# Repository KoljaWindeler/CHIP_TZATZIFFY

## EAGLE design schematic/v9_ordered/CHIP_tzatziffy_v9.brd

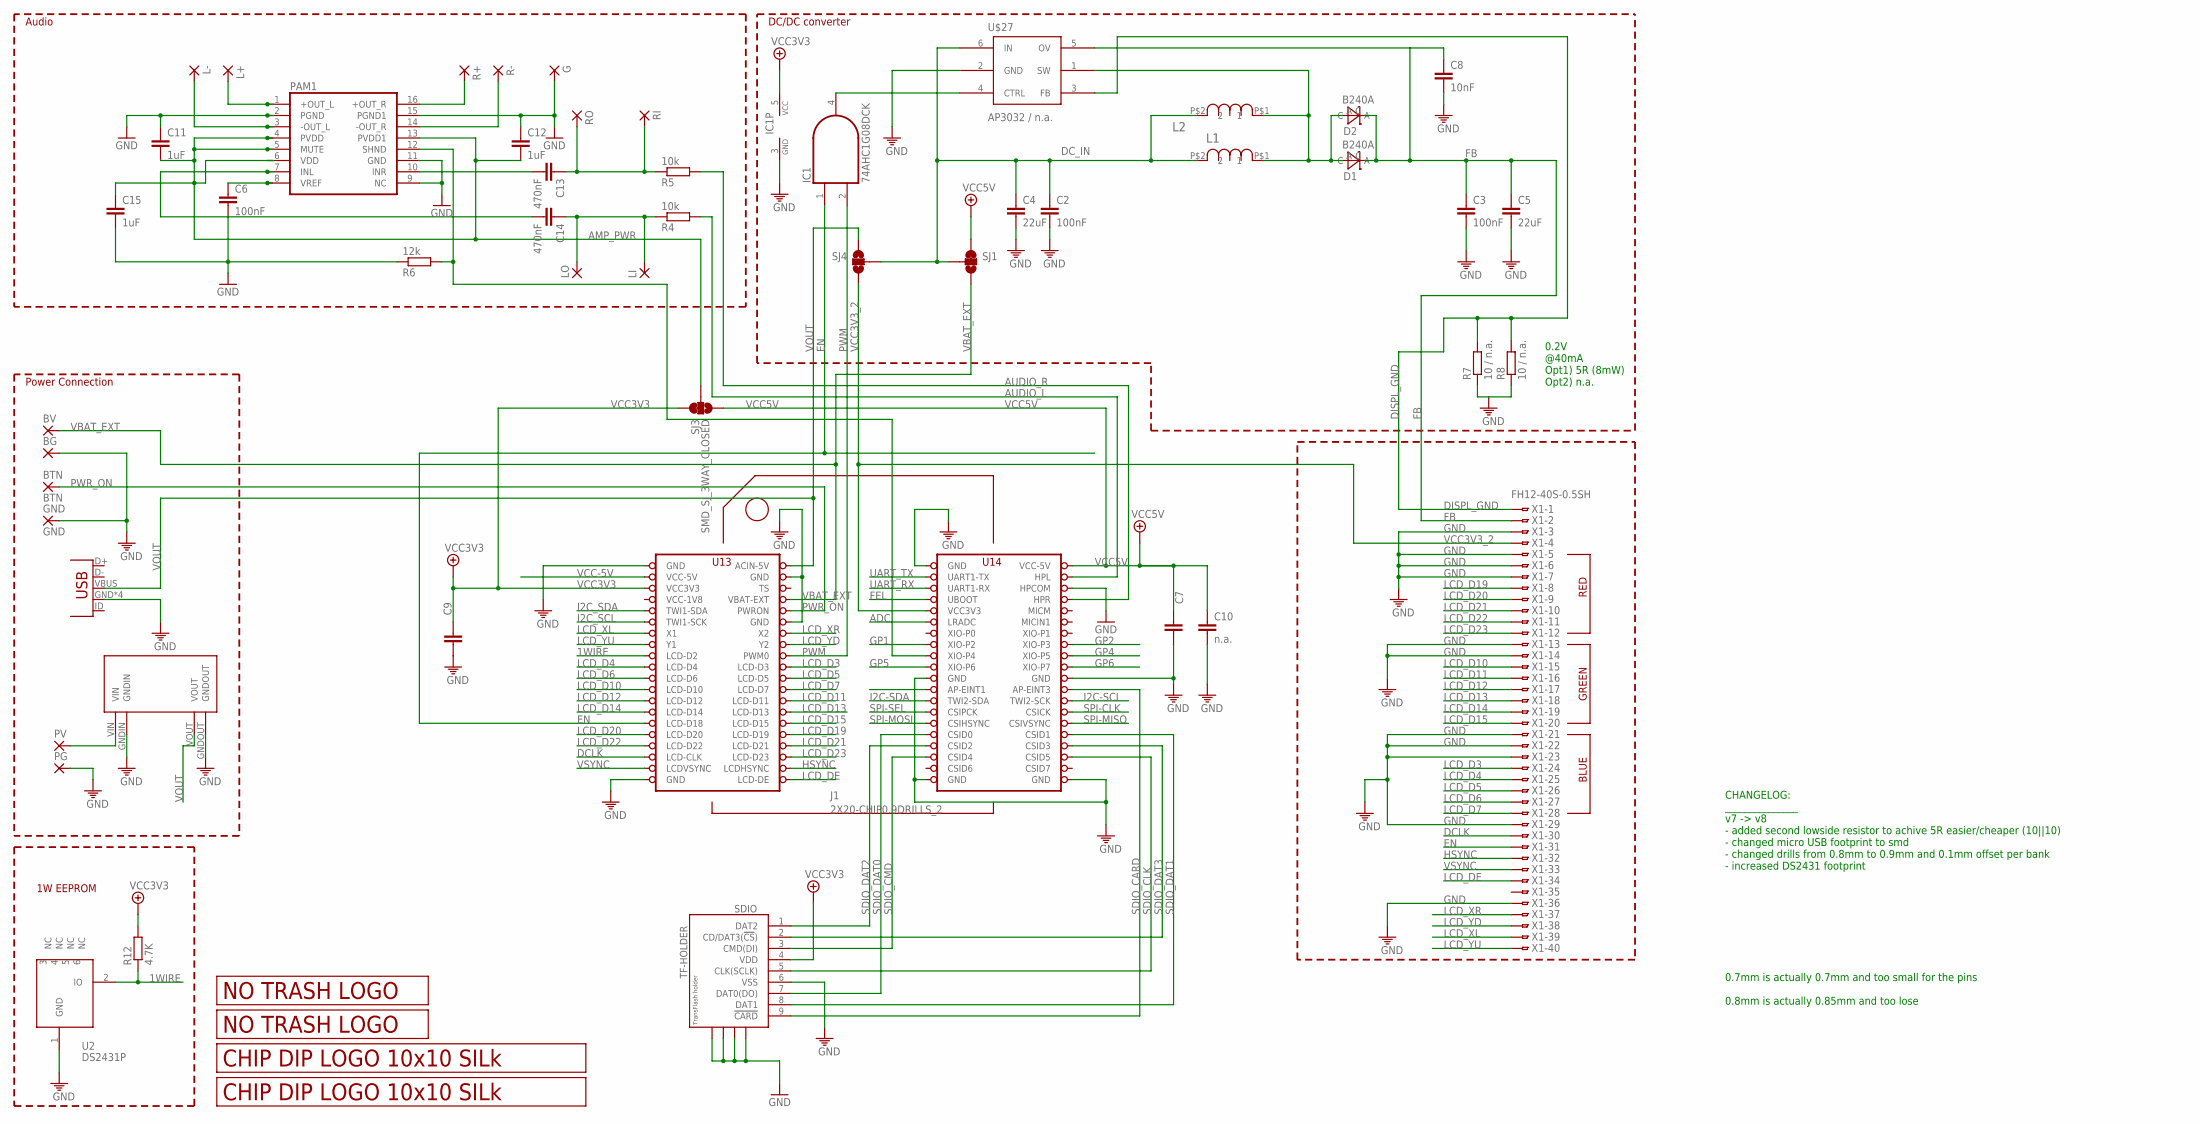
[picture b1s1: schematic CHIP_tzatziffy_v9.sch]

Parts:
BG: 1,6/0,8
BTN: BTN; SMD1,27-2,54
BV: 1,6/0,8
C2, C3, C6: 100nF; C0805
C4, C5: 22uF; C1206
C7, C9, C10: n.a.; C0805
C8: 10nF; C0805
C11, C12, C15: 1uF; C0805
C13, C14: 470nF; C0805
D1, D2: B240A; DO-214AC
G: 1,6/0,8
GND: GND; SMD1,27-2,54
IC1: 74AHC1G08DCK; SC70-5
J1: 2X20-CHIP0.9DRILLS_2; 2X20CHIP_BANK_OFFSET_TH_0.9
JP1: USBMICRO_SMD; USB-B-MICRO-SMD_V03
L1, L2: SRN6045-100M; SRN6045
L+: 1,6/0,8
L-: 1,6/0,8
LI: 1,6/0,8
LO: 1,6/0,8
PAM1: PAM8403; SOP-16
PG: 1,6/0,8
PV: 1,6/0,8
R4, R5: 10k; R0805
R6: 12k; R0805
R7, R8: 10 / n.a.; M0805
R12: 4.7K; M0805
R+: 1,6/0,8
R-: 1,6/0,8
RI: 1,6/0,8
RO: 1,6/0,8
SDIO: TF-HOLDER; TF-PULL
SJ1, SJ3: SMD_SJ_3WAY_CLOSED
SJ4: SMD_SJ_3WAY_OPENT; SMD_SJ_3WAY_OPEN
U2: DS2431P; TSOC6
U$2, U$5: LOGO_10X10_SILK; LOGO2_10X10_SILK
U$3: LOGO_NO_TRASHROHS; LOGO_ROHS_SYM
U$4: LOGO_NO_TRASHNO_TRASH; LOGO_ROHS_NO_TRASH
U$10: MP1584EN_FRAMELESS
U$27: AP3032 / n.a.; SOT23-6
X1: FH12-40S-0.5SH

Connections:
1WIRE: J1.LCD-D2, R12.1, U2.2 (IO)
ADC: J1.LRADC
AMP_PWR: C11.2, C12.2, C15.1, PAM1.4 (PVDD), PAM1.5 (MUTE), PAM1.6 (VDD), PAM1.13 (PVDD1), SJ3.2
AUDIO_L: J1.HPL, R4.2
AUDIO_R: J1.HPR, R5.2
DCLK: J1.LCD-CLK, X1.30
DC_IN: C2.1, C4.1, L1.P$2 (2), L2.P$2 (2), SJ1.2, SJ4.2, U$27.6 (IN)
DISPL_GND: R7.2, R8.2, U$27.3 (FB), X1.1
EN: IC1.1 (I0), J1.LCD-D18, X1.31
FB: C3.1, C5.1, C8.1, D1.C, D2.C, U$27.5 (OV), X1.2
FEL: J1.FEL (UBOOT)
GND: BG.1, C2.2, C3.2, C4.2, C5.2, C6.2, C7.2, C8.2, C9.2, C10.2, C11.1, C12.1, C15.2, G.1, GND.1, IC1.3 (GND), J1.GND@1 (GND), J1.GND@2 (GND), J1.GND@3 (GND), J1.GND@4 (GND), J1.GND@5 (GND), J1.GND@6 (GND), J1.GND@7 (GND), J1.GND@8 (GND), J1.GND@10 (GND), J1.HPCOM, JP1.GND, JP1.SHIELD1 (GND), JP1.SHIELD2 (GND), JP1.SHIELD3 (GND), PAM1.2 (PGND), PAM1.9 (NC), PAM1.11 (GND), PAM1.15 (PGND1), PG.1, R6.1, R7.1, R8.1, SDIO.6 (VSS), SDIO.S1, SDIO.S2, SDIO.S3, SDIO.S4, U2.1 (GND), U$10.GNDIN, U$10.GNDOUT, U$27.2 (GND), X1.3, X1.5, X1.6, X1.7, X1.13, X1.14, X1.21, X1.22, X1.23, X1.29, X1.36
GP1: J1.XIO-P2
GP2: J1.XIO-P3
GP3: J1.XIO-P4, PAM1.12 (SHND), R6.2
GP4: J1.XIO-P5
GP5: J1.XIO-P6
GP6: J1.XIO-P7
HSYNC: J1.LCD-HSYNC (LCDHSYNC), X1.32
I2C-SCL: J1.TWI2-SCK
I2C-SDA: J1.TWI2-SDA
I2C_SCL: J1.TWI1-SCK
I2C_SDA: J1.TWI1-SDA
INL: C14.2, PAM1.7 (INL)
INR: C13.2, PAM1.10 (INR)
KPD_INT: J1.AP-EINT1
L+OUT: L+.1, PAM1.1 (+OUT_L)
L-OUT: L-.1, PAM1.3 (-OUT_L)
LCD_D3: J1.LCD-D3, X1.24
LCD_D4: J1.LCD-D4, X1.25
LCD_D5: J1.LCD-D5, X1.26
LCD_D6: J1.LCD-D6, X1.27
LCD_D7: J1.LCD-D7, X1.28
LCD_D10: J1.LCD-D10, X1.15
LCD_D11: J1.LCD-D11, X1.16
LCD_D12: J1.LCD-D12, X1.17
LCD_D13: J1.LCD-D13, X1.18
LCD_D14: J1.LCD-D14, X1.19
LCD_D15: J1.LCD-D15, X1.20
LCD_D19: J1.LCD-D19, X1.8
LCD_D20: J1.LCD-D20, X1.9
LCD_D21: J1.LCD-D21, X1.10
LCD_D22: J1.LCD-D22, X1.11
LCD_D23: J1.LCD-D23, X1.12
LCD_DE: J1.LCD-DE, X1.34
LCD_XL: J1.X1, X1.39
LCD_XR: J1.X2, X1.37
LCD_YD: J1.Y2, X1.38
LCD_YU: J1.Y1, X1.40
unnamed: IC1.4 (O), U$27.4 (CTRL)
unnamed: C6.1, PAM1.8 (VREF)
unnamed: C14.1, LI.1, LO.1, R4.1
unnamed: C13.1, R5.1, RI.1, RO.1
PWM: IC1.2 (I1), J1.PWM0
PWR_IN: PV.1, U$10.VIN
PWR_ON: BTN.1, J1.PWRON
R+OUT: PAM1.16 (+OUT_R), R+.1
R-OUT: PAM1.14 (-OUT_R), R-.1
SDIO_CARD: J1.AP-EINT3, SDIO.9 (!CARD)
SDIO_CLK: J1.CSID5, SDIO.5 (CLK(SCLK))
SDIO_CMD: J1.CSID4, SDIO.3 (CMD(DI))
SDIO_DAT0: J1.CSID0, SDIO.7 (DAT0(DO))
SDIO_DAT1: J1.CSID1, SDIO.8 (DAT1)
SDIO_DAT2: J1.CSID2, SDIO.1 (DAT2)
SDIO_DAT3: J1.CSID3, SDIO.2 (CD/DAT3(!CS!))
SPI-CLK: J1.CSICK
SPI-MISO: J1.CSIVSYNC
SPI-MOSI: J1.CSIHSYNC
SPI-SEL: J1.CSIPCK
UART_RX: J1.UART1-RX
UART_TX: J1.UART1-TX
VBAT_EXT: BV.1, J1.BAT (VBAT-EXT), SJ1.3
VCC3V3: C9.1, IC1.5 (VCC), J1.VCC3V3, R12.2, SDIO.4 (VDD), SJ3.1
VCC3V3_2: J1.VCC3V3@1 (VCC3V3), SJ4.3, X1.4
VCC5V: C7.1, C10.1, J1.VCC5V@1 (VCC-5V), SJ1.1, SJ3.3
VCC-1V8: J1.VCC1V8 (VCC-1V8)
VCC-5V: J1.VCC5V@0 (VCC-5V)
VOUT: J1.CHG-IN (ACIN-5V), JP1.VBUS, SJ4.1, U$10.VOUT
VREG_OUTPUT: D1.A, D2.A, L1.P$1 (1), L2.P$1 (1), U$27.1 (SW)
VSYNC: J1.LCD-VSYNC (LCDVSYNC), X1.33

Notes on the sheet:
RED
GREEN
BLUE
Power Connection
1W EEPROM
Audio
DC/DC converter
0.2V @40mA Opt1) 5R (8mW) Opt2) n.a.
0.7mm is actually 0.7mm and too small for the pins 0.8mm is actually 0.85mm and too lose
CHANGELOG: _______________ v7 -> v8 - added second lowside resistor to achive 5R easier/cheaper (10||10) - changed micro USB footprint to smd - changed drills from 0.8mm to 0.9mm and 0.1mm offset per bank - increased DS2431 footprint

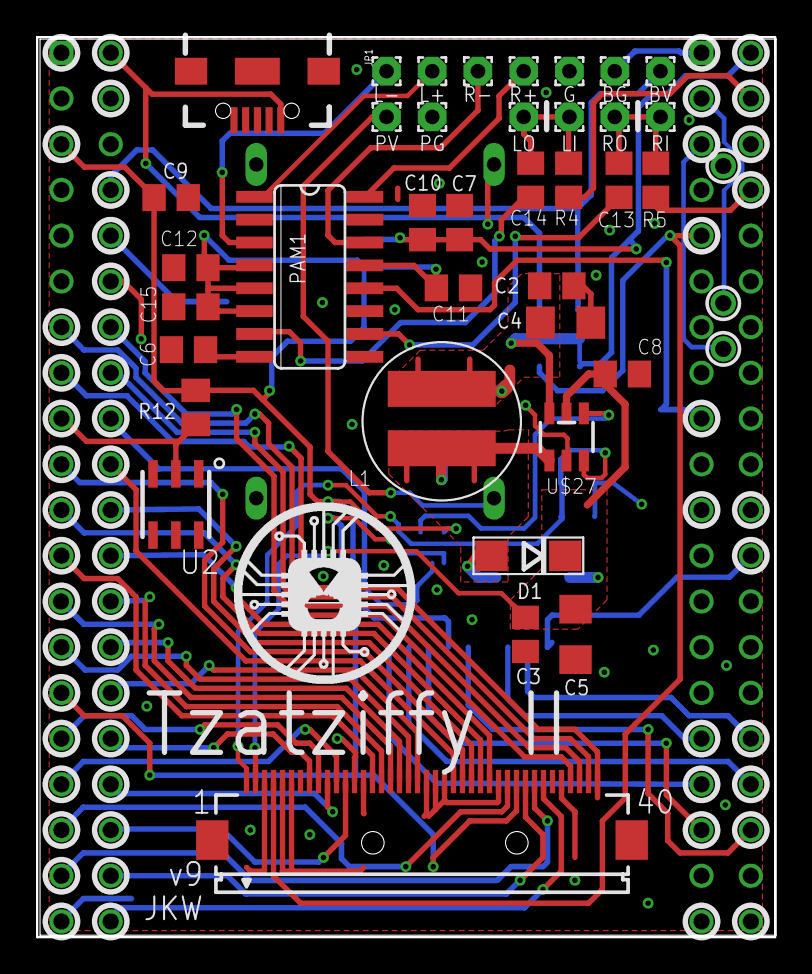
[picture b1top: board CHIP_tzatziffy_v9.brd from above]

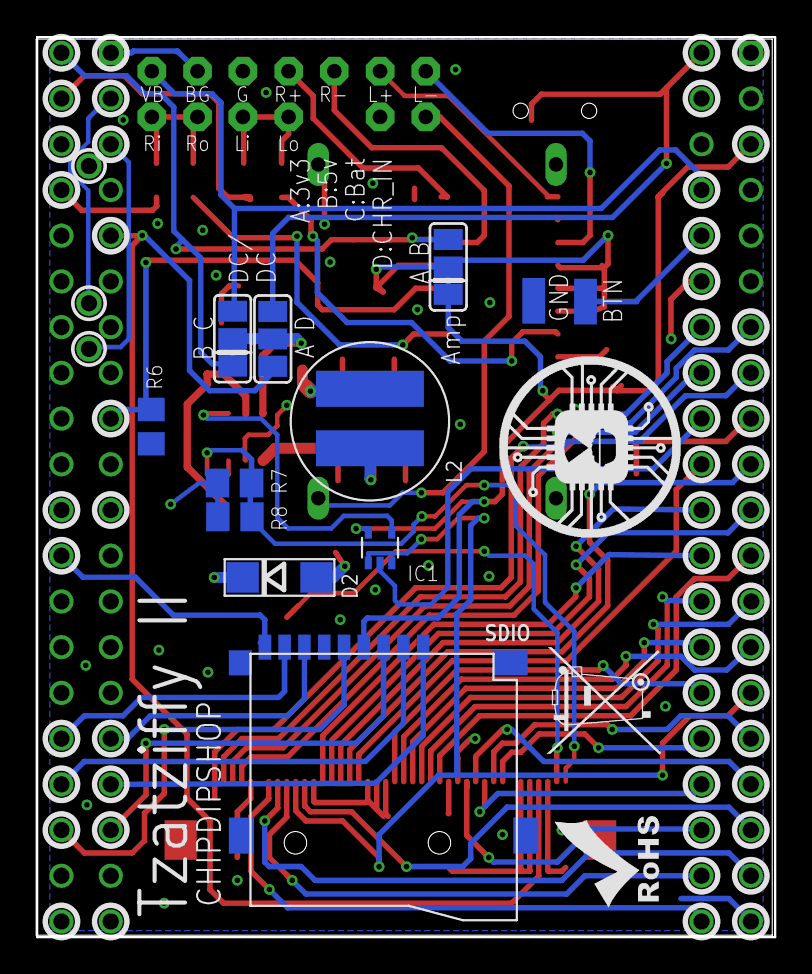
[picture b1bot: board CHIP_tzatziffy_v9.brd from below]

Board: 2 copper layers, 41.0 x 50.0 mm, 55 parts (15 on the bottom side), 60 nets.

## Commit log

2016-08-28 init
2016-08-28 added solder marks
2016-08-28 moved sd to right
2016-08-29 added v3 incl gerber
2016-08-29 recalc resistor to generate 19.2V
2016-08-31 Added Descriptions
2016-09-02 added v4, with battery to 5v switch
2016-09-08 added v5 with correct mute potential
2016-09-15 Optimized routing, added symbols
2016-09-15 moved v5 to ordered_v5
2016-09-15 added ignore
2016-09-15 added diode on bottom
2016-09-16 added elecrow rulecheck and fixed details
2016-09-18 Added connection for poti
2016-09-18 added pulldown for shutdown
2016-09-18 added note for pulldown
2016-09-18 changed pulldown to assembled
2016-09-21 added note for correct voltage divider
2016-09-21 added datasheets
2016-09-22 changed 22uF Footprint to 1206
2016-09-22 added overlay for tzatziffy
2016-09-23 Adding scripts and quote
2016-09-26 added flickr prj
2016-09-26 added ignore settings
2016-09-26 removed settings
2016-09-26 added empty settings file
2016-09-26 added settings to ignore list
2016-09-26 reenabled PIL
2016-09-26 exit if not all flicker details availble
2016-09-26 loading label added
2016-09-26 added dts
2016-09-26 Added pads for power button and vias for the uart header
2016-09-26 added orange text and removed frame
2016-09-26 avoid dual start handles
2016-09-26 added install
2016-09-28 changed poti pins to smaller restring, added jumper for 3.3/5/vbat for DC/DC and 3.3/5 for audio amp
2016-09-28 added davids xorg
2016-09-29 added no-mouse
2016-09-29 replaced bipolar with mosfet circuit and relayouted
2016-09-29 added start script
2016-09-30 simplyfied the backlight driver ... a lot
2016-09-30 added adafruit 10v datasheet
2016-09-30 changed holes size to 0.7mm
2016-09-30 moved silkscreen label
2016-09-30 updated gerber
2016-09-30 removed old gerber
2016-09-30 renamed v6 to ordered
2016-09-30 Add datasheets
2016-10-01 added album mode
2016-10-01 updated start script with anti blanking
2016-10-03 Added setup script
2016-10-03 separated functions
2016-10-03 recall update album image
2016-10-03 added splash
2016-10-03 centerlized time
2016-10-03 added right click
2016-10-06 added micro usb port
2016-10-07 improved routing
2016-10-07 added power supply
2016-10-07 optimized routing
2016-10-07 optimized routing and schematic
2016-10-07 added eeprom img and howdo
2016-10-08 added public photo by search term support
2016-10-08 added git to prepare script
2016-10-08 added apt update
2016-10-08 added autorun
2016-10-08 added helper cmd
2016-10-08 added print photo info and optimized search a lot!
2016-10-08 add whitspaces in search string
2016-10-08 set search tag to ford mustang
2016-10-09 added dc/dc alternate switch
2016-10-09 added alternate dc/dc switch
2016-10-09 fixed airwire
2016-10-11 moved to ordered
2016-10-13 added v8 with quotation, only added second resistor footprint to ease up the R||R combination e.g. to achive 5R as 10R || 10R
2016-10-13 added radio scripts
2016-10-14 updated quote v8
2016-10-15 added broken picture detect mode
2016-10-15 added image conversion modes (black/white)
2016-10-15 added prepare script
2016-10-15 added -y to apt install
2016-10-15 added sepia
2016-10-16 added pchip eeprom
2016-10-17 .\quotations\v8\PCBA_with_elecrow_quotation_tzatziffy_v8.xlsx
    updated elecrow quote
2016-10-17 added prices for 0 count parts
2016-10-18 added usb jack to quote
2016-10-18 use of new usb lib
2016-10-18 changed 22uF cap to 1210
2016-10-19 updated cost for 22uF
2016-10-19 added new smd usb
2016-10-20 updated smd usb jack
2016-10-25 changed chip footprint to clamp via row claming 0.1mm outside and ordered v8
2016-10-25 added reference to maxime's original dts
2016-10-25 added and gate
2016-10-27 inverted PWM
2016-10-27 working dtc compiler and pwm
2016-10-28 added 4.4 support
2016-10-29 display switch script
2016-10-30 moved overlay code in two subsection to load display on boot and sd card after boot
2016-10-30 reordered files
2016-10-30 changed load script to correct dtbo
2016-10-30 added run right
2016-10-30 added run rights
2016-11-02 added psp screen modification drawing
2016-11-04 added keyboard overlay
2016-11-09 removed psp schematic, see separate respo
2016-11-09 added install script
2016-11-10 added version9, working fine, ready for production
2016-12-08 replaced quote
2016-12-08 added solder docu
2016-12-18 clean up
2017-02-21 simple install script
2017-02-22 added tester
2017-02-22 added extended info
2017-02-22 added version
2017-04-06 added pdf
2017-04-18 added v7
2017-05-03 Added headers to all scripts so that Ansible recognizes them

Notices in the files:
parts and their libraries:
JKW_CHIP: License : http://creativecommons.org/licenses/by-sa/3.0
(Creative Commons 3.0)
